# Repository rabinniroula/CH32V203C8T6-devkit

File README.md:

# CH32V203 Devkit Homebrew PCB

**docs to follow soon**

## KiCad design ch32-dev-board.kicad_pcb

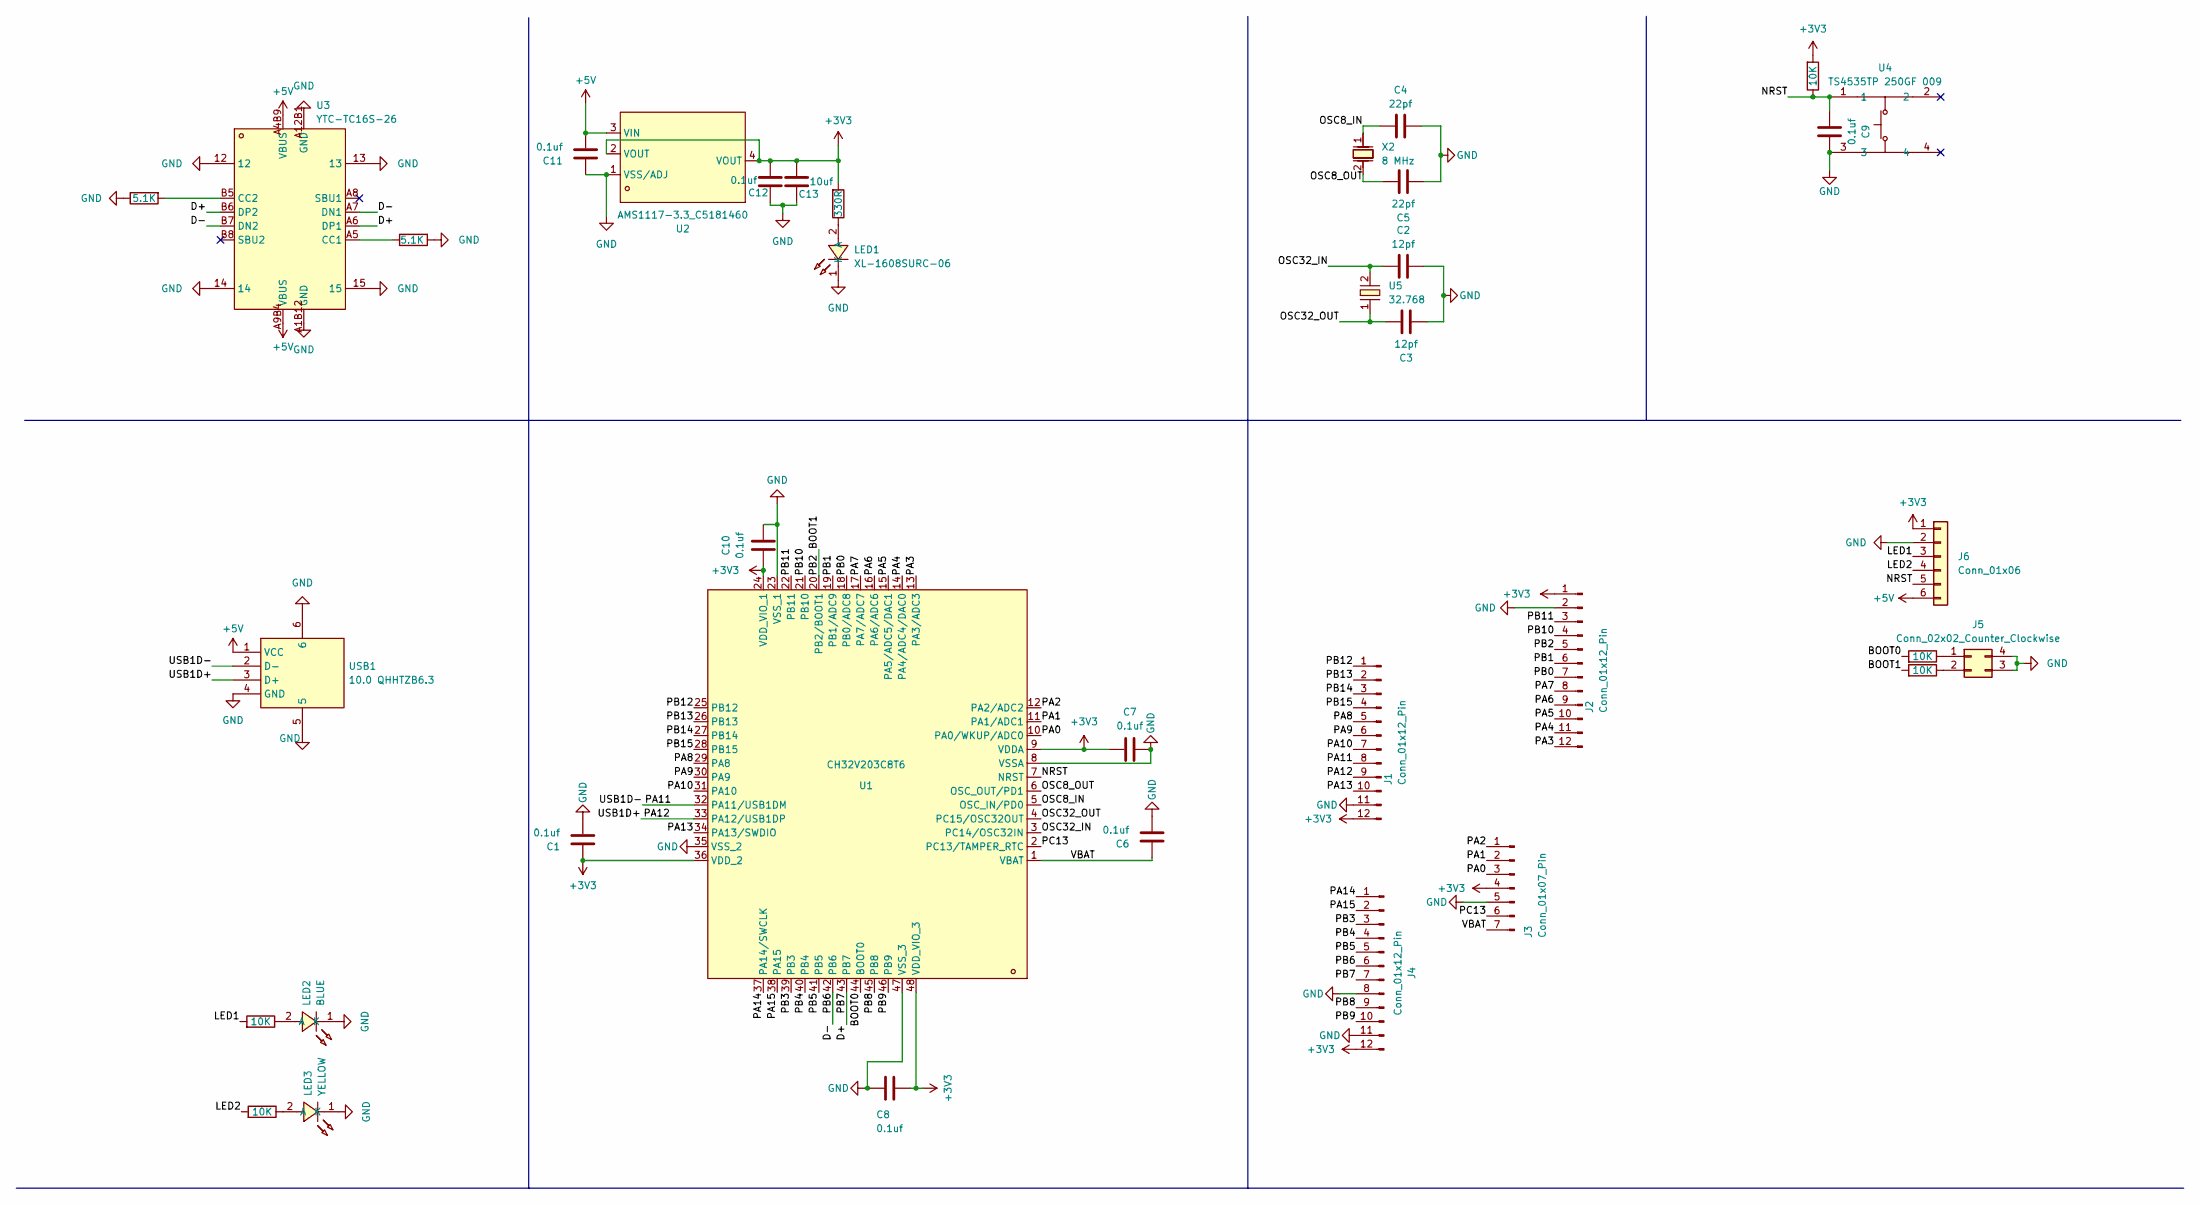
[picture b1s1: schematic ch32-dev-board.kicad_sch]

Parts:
C1, C6, C7, C8, C9, C10, C11, C12: 0.1uf; C_0603_1608Metric_Pad1.08x0.95mm_HandSolder
C2, C3: 12pf; C_0603_1608Metric_Pad1.08x0.95mm_HandSolder
C4, C5: 22pf; C_0603_1608Metric_Pad1.08x0.95mm_HandSolder
C13: 10uf; C_0603_1608Metric_Pad1.08x0.95mm_HandSolder
J1, J2, J4: Conn_01x12_Pin; PinHeader_1x12_P2.54mm_Vertical
J3: Conn_01x07_Pin; PinHeader_1x07_P2.54mm_Vertical
J5: Conn_02x02_Counter_Clockwise; PinHeader_2x02_P2.54mm_Vertical
J6: Conn_01x06; PinHeader_1x06_P2.54mm_Vertical
LED1: XL-1608SURC-06; LED0603-RD_RED; LCSC Part C965799
LED2: BLUE; LED0603-RD_RED; LCSC Part C965799
LED3: YELLOW; LED0603-RD_RED; LCSC Part C965799
R1, R2: 5.1K; R_0603_1608Metric_Pad0.98x0.95mm_HandSolder
R3, R5, R6, R7, R8: 10K; R_0603_1608Metric_Pad0.98x0.95mm_HandSolder
R4: 330R; R_0603_1608Metric_Pad0.98x0.95mm_HandSolder
U1: CH32V203C8T6; LQFP-48_L7.0-W7.0-P0.50-LS9.0-BL; LCSC Part C3001172
U2: AMS1117-3.3_C5181460; SOT-223-3_L6.4-W3.5-P2.30-LS7.0-BR; LCSC Part C5181460
U3: YTC-TC16S-26; USB-C-SMD_YTC-TC16S-26-A; LCSC Part C2927292
U4: TS4535TP 250GF 009; SW-SMD_4P-L4.5-W4.5-P3.00-LS6.8; LCSC Part C5342982
U5: 32.768; CRYSTAL-SMD_L3.2-W1.5-1; LCSC Part C5361379
USB1: 10.0 QHHTZB6.3; OST_USB-A1HSW6; LCSC Part C668591
X2: 8 MHz; CRYSTAL-SMD_L11.5-W4.8-LS12.7; LCSC Part C12674

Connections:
+3V3: C1.1, C7.2, C8.1, C10.2, C12.2, C13.2, J1.12, J2.1, J3.4, J4.12, J6.1, R3.2, R4.2, U1.9 (VDDA), U1.24 (VDD_VIO_1), U1.36 (VDD_2), U1.48 (VDD_VIO_3), U2.2 (VOUT), U2.4 (VOUT)
+5V: C11.2, J6.6, U2.3 (VIN), U3.A4B9 (VBUS), U3.A9B4 (VBUS), USB1.1 (VCC)
/BOOT0: R7.2, U1.44 (BOOT0)
/BOOT1: J2.5, R8.2, U1.20 (PB2/BOOT1)
/D+: J4.7, U1.43 (PB7), U3.A6 (DP1), U3.B6 (DP2)
/D-: J4.6, U1.42 (PB6), U3.A7 (DN1), U3.B7 (DN2)
/LED1: J6.3, R5.2
/LED2: J6.4, R6.2
/NRST: C9.1, J6.5, R3.1, U1.7 (NRST), U4.1
/OSC8_IN: C4.1, U1.5 (OSC_IN/PD0), X2.1
/OSC8_OUT: C5.1, U1.6 (OSC_OUT/PD1), X2.2
/OSC32_IN: C2.1, U1.3 (PC14/OSC32IN), U5.2
/OSC32_OUT: C3.1, U1.4 (PC15/OSC32OUT), U5.1
/PA0: J3.3, U1.10 (PA0/WKUP/ADC0)
/PA1: J3.2, U1.11 (PA1/ADC1)
/PA2: J3.1, U1.12 (PA2/ADC2)
/PA3: J2.12, U1.13 (PA3/ADC3)
/PA4: J2.11, U1.14 (PA4/ADC4/DAC0)
/PA5: J2.10, U1.15 (PA5/ADC5/DAC1)
/PA6: J2.9, U1.16 (PA6/ADC6)
/PA7: J2.8, U1.17 (PA7/ADC7)
/PA8: J1.5, U1.29 (PA8)
/PA9: J1.6, U1.30 (PA9)
/PA10: J1.7, U1.31 (PA10)
/PA11: J1.8, U1.32 (PA11/USB1DM), USB1.2 (D-)
/PA12: J1.9, U1.33 (PA12/USB1DP), USB1.3 (D+)
/PA13: J1.10, U1.34 (PA13/SWDIO)
/PA14: J4.1, U1.37 (PA14/SWCLK)
/PA15: J4.2, U1.38 (PA15)
/PB0: J2.7, U1.18 (PB0/ADC8)
/PB1: J2.6, U1.19 (PB1/ADC9)
/PB3: J4.3, U1.39 (PB3)
/PB4: J4.4, U1.40 (PB4)
/PB5: J4.5, U1.41 (PB5)
/PB8: J4.9, U1.45 (PB8)
/PB9: J4.10, U1.46 (PB9)
/PB10: J2.4, U1.21 (PB10)
/PB11: J2.3, U1.22 (PB11)
/PB12: J1.1, U1.25 (PB12)
/PB13: J1.2, U1.26 (PB13)
/PB14: J1.3, U1.27 (PB14)
/PB15: J1.4, U1.28 (PB15)
/PC13: J3.6, U1.2 (PC13/TAMPER_RTC)
/VBAT: C6.1, J3.7, U1.1 (VBAT)
GND: C1.2, C2.2, C3.2, C4.2, C5.2, C6.2, C7.1, C8.2, C9.2, C10.1, C11.1, C12.1, C13.1, J1.11, J2.2, J3.5, J4.8, J4.11, J5.3, J5.4, J6.2, LED1.1 (K), LED2.1 (K), LED3.1 (K), R1.1, R2.2, U1.8 (VSSA), U1.23 (VSS_1), U1.35 (VSS_2), U1.47 (VSS_3), U2.1 (VSS/ADJ), U3.12, U3.13, U3.14, U3.15, U3.A1B12 (GND), U3.A12B1 (GND), U4.3, USB1.4 (GND), USB1.5, USB1.6
unnamed: J5.1, R7.1
unnamed: J5.2, R8.1
unnamed: LED1.2 (A), R4.1
unnamed: LED2.2 (A), R5.1
unnamed: LED3.2 (A), R6.1
unnamed: R2.1, U3.A5 (CC1)
unnamed: R1.2, U3.B5 (CC2)

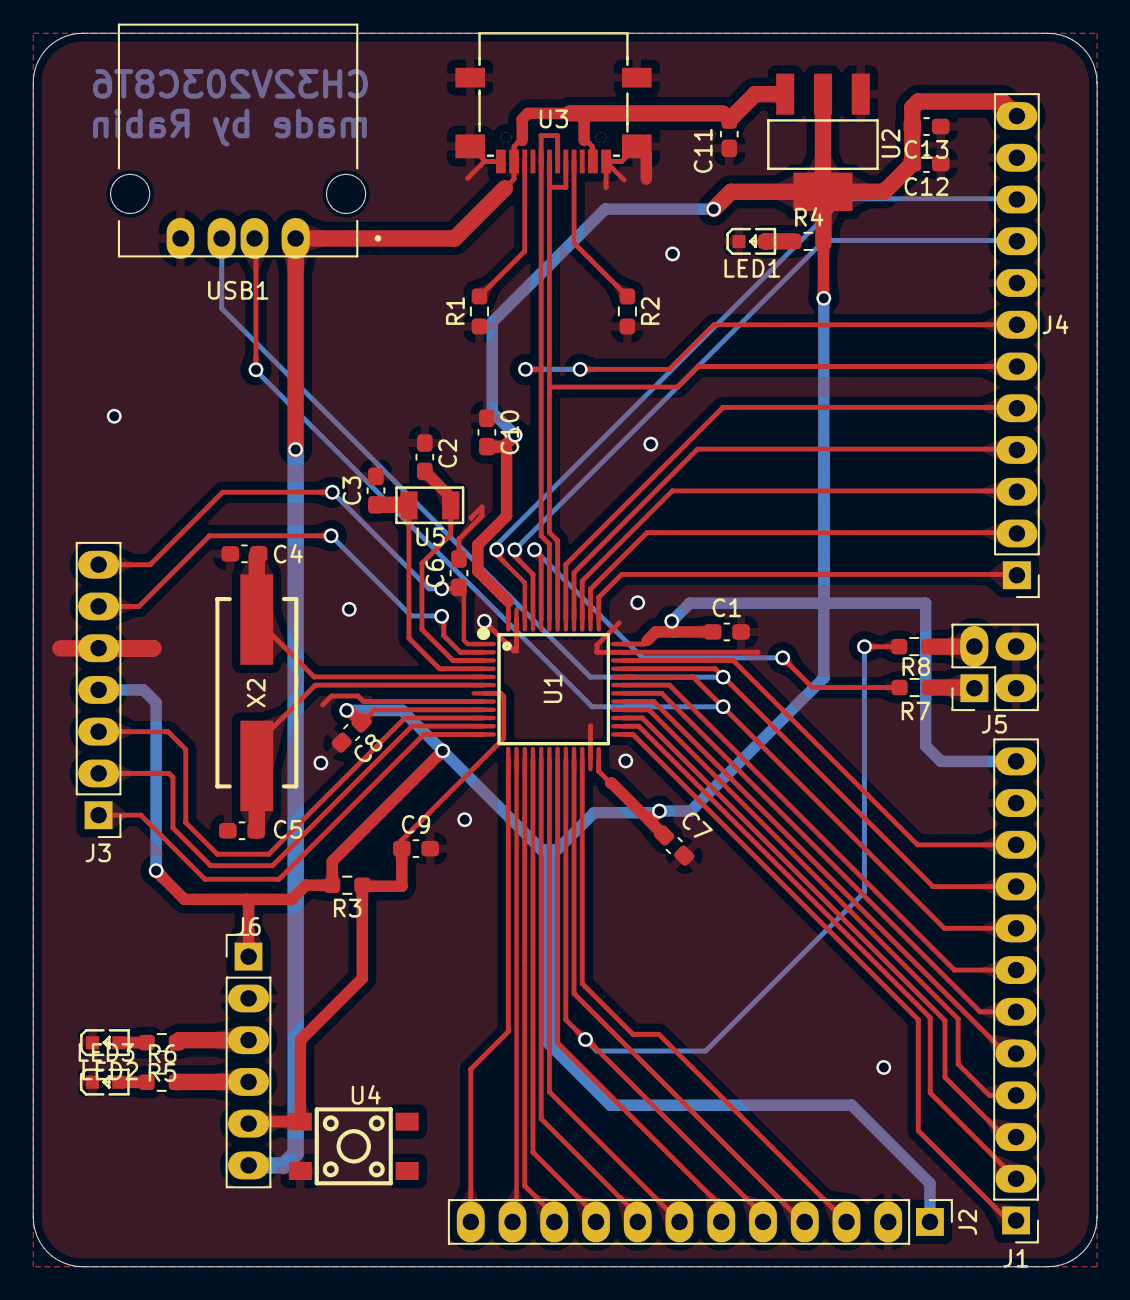
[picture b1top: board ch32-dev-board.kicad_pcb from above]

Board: 2 copper layers, 64.7 x 75.0 mm, 37 parts (0 on the bottom side), 52 nets.

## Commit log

2025-04-06 init
2025-04-06 added readme
2025-04-06 fixed the pic
